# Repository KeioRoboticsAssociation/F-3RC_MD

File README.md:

# モータドライバ（SN754410NE）基板

[SN754410NEのデータシート](http://akizukidenshi.com/download/ds/ti/SN754410NE.pdf)

## この基板を設計した経緯

モータードライバは壊れやすい。そのたびにユニバーサル基板で作りなおすと
結構キツい。それに大会間近に故障で試験走行ができない時間ができると
超もったいない。どうせ同じものを複数個作るなら、プリント基板でキット化して、
ドライバ故障→交換までのストレスを減らそう！ってこと。それだけ。
　一応、1年生が参加することになってるF^RC用に使うことを考えて始めた計画だけど、
あとに書くスペックを見て、自分の要求を満たしているならなんでも使えると思う。

## 仕様

詳しいことはデータシートを読んだ方がいいと思うので、使う上で必要そうなこと
だけをまとめておく。

| 場所         | 特性                                                          |
|--------------|---------------------------------------------------------------|
| ロジック電源 | 4.5〜5.5V（2.1mｍ標準DCコネクタ）                             |
| モーター電源 | 4.5〜36V（2.1mｍ標準DCコネクタ）                              |
| 出力         | ピンヘッダ or ピンソケット1x8                                 |
| 入力         | デジタル入力・PWM（High=2〜5.5V、Low=-0.3〜0.8V、ピンソケット） |

ICひとつにハーフブリッジ回路が４つ入っている。モーターを正転・逆転させたい、
またはブレーキをかけたい場合はICひとつでモーター2個駆動できる。また、モーターを
一方向にしか回さない、かつブレーキはいらない場合はICひとつで
モーター4個駆動できる。ここで注意してほしいのは、
「ブレーキがかけられない≠止まらない」だということ
（モーターの電源を切ればしばらく走って止まる）。

INPUTピンの番号は、左(DCコネクタがある方)から順にA1, A2, A3, A4, A1, A2, A3, A4
になっている。同様にOUTPUTピンの番号はY1, Y2, Y3, Y4, Y1, Y2, Y3, Y4になっている。
AピンとYピンは1対1対応してる。入力AがHighなら向かい合う出力YもHigh。
Lowの場合も同じ。詳しくはデータシートの図を見てほしい。

ちなみにENピンはICに含まれる回路の半分だけ電源を切りたいときとかに使える
ようだが、このプリント基板では常にHighになるよう設計されている。

## 部品表

| 番号（基板に書いてある） | 部品名（秋月のホームページとかで調べて） | 個数 | 備考                                                                                |
|--------------------------|------------------------------------------|------|-------------------------------------------------------------------------------------|
| P1, P2                   | 基板取り付け用DCジャック                 | 2    | センタープラス（中心の棒プラス）だよ。                                              |
| P3, P4                   | ピンヘッダ or ピンソケット1x8            | 2    | 挿す方でも挿される方でもご自由に。                                                  |
| C1, C3                   | 電解コンデンサ(100μF 35V)                | 2    | 直径6.3mm以上のコンデンサだと周りの部品に干渉するかも。足の長い方がプラスに繋がる。 |
| C2, C4                   | 積層セラミックコンデンサ(0.4μF 50V)      | 2    |                                                                                     |
| U1, U2                   | モータードライバIC（SN754410NE）         | 2    | 実際はんだ付けするのはICソケット（16P）にした方がいいよ。                           |

## 外観

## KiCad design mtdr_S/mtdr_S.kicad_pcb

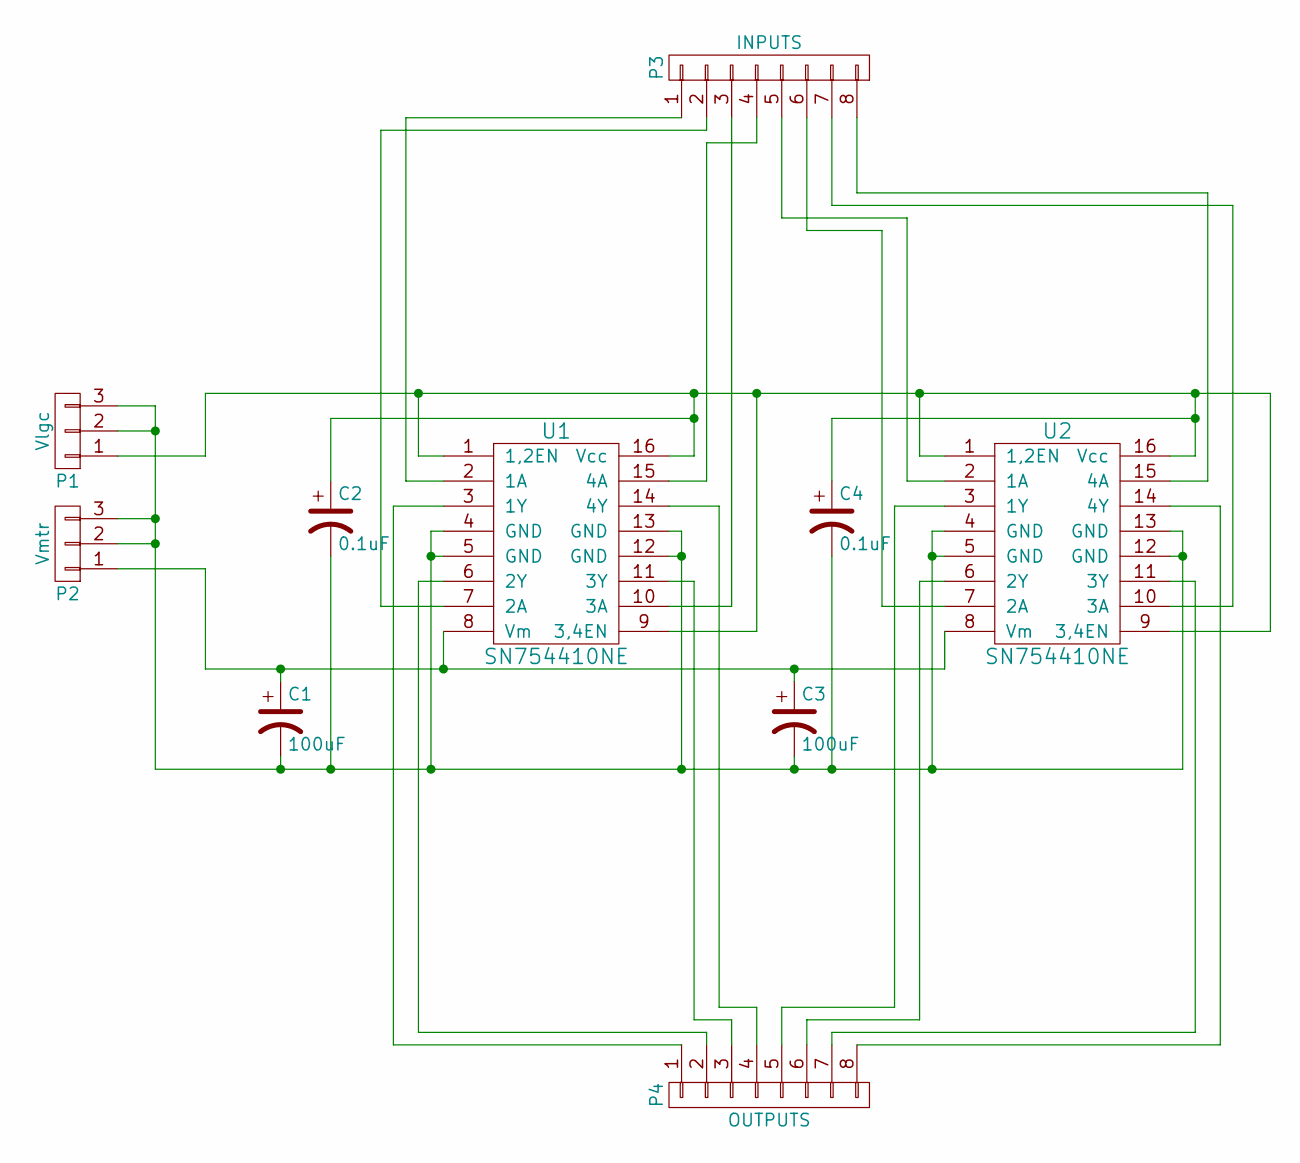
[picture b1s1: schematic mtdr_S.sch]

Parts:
C1, C3: 100uF; CP_Radial_D6.3mm_P2.50mm
C2, C4: 0.1uF; C_Disc_D5.0mm_W2.5mm_P5.00mm
P1: Vlgc; BARREL_JACK
P2: Vmtr; BARREL_JACK
P3: INPUTS; Pin_Header_Straight_1x08_Pitch2.54mm
P4: OUTPUTS; Pin_Header_Straight_1x08_Pitch2.54mm
U1, U2: SN754410NE; DIP-16_W7.62mm

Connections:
unnamed: C1.1, C3.1, P2.1, U1.8 (Vm), U2.8 (Vm)
unnamed: C1.2, C2.2, C3.2, C4.2, P1.2, P1.3, P2.2, P2.3, U1.4 (GND), U1.5 (GND), U1.12 (GND), U1.13 (GND), U2.4 (GND), U2.5 (GND), U2.12 (GND), U2.13 (GND)
unnamed: C2.1, C4.1, P1.1, U1.1 (1,2EN), U1.9 (3,4EN), U1.16 (Vcc), U2.1 (1,2EN), U2.9 (3,4EN), U2.16 (Vcc)
unnamed: P3.1, U1.2 (1A)
unnamed: P3.2, U1.7 (2A)
unnamed: P3.3, U1.10 (3A)
unnamed: P3.4, U1.15 (4A)
unnamed: P3.5, U2.2 (1A)
unnamed: P3.6, U2.7 (2A)
unnamed: P3.7, U2.10 (3A)
unnamed: P3.8, U2.15 (4A)
unnamed: P4.1, U1.3 (1Y)
unnamed: P4.2, U1.6 (2Y)
unnamed: P4.3, U1.11 (3Y)
unnamed: P4.4, U1.14 (4Y)
unnamed: P4.5, U2.3 (1Y)
unnamed: P4.6, U2.6 (2Y)
unnamed: P4.7, U2.11 (3Y)
unnamed: P4.8, U2.14 (4Y)

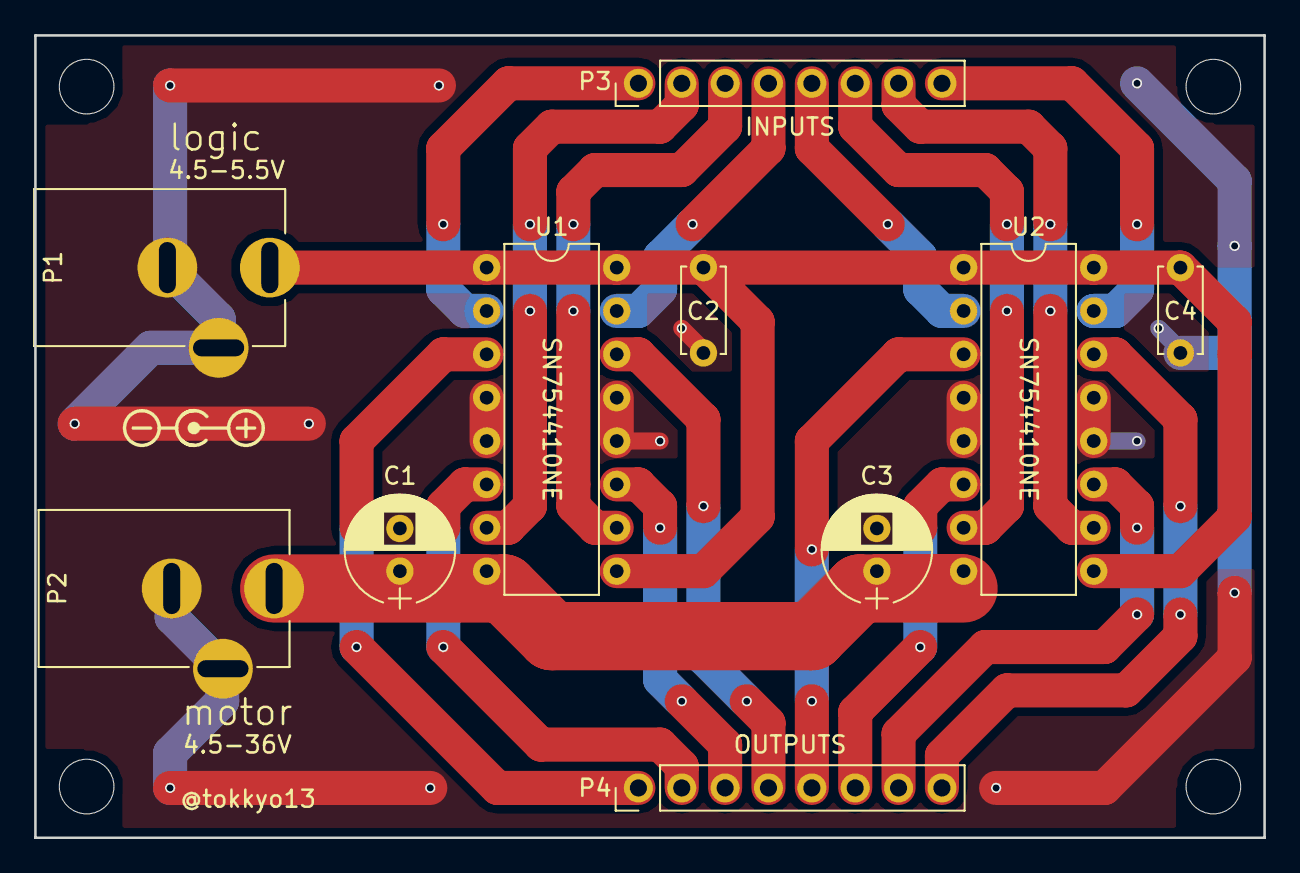
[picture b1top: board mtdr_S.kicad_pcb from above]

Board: 2 copper layers, 72.0 x 47.0 mm, 10 parts (0 on the bottom side), 19 nets.

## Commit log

2017-06-19 add new file
2017-06-19 説明書に少し変更を加えた
2017-06-19 deleted DS_Store
2017-06-19 add pdf file
2017-06-19 ignore
2017-06-19 add gitignore
2017-06-19 余計なファイル消した
2017-06-26 schを追加
2017-06-26 move documentation to Markdown
2017-06-26 add images
2017-06-26 fix rotation
2017-06-26 add table
2017-06-26 remove datasheet from repo
2017-06-26 add relevant files
2017-06-26 fix strikethrough
